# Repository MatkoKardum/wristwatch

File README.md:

# Project Name

## Overview
This project is an electronics/embedded systems project that involves firmware development, PCB design, simulation, and documentation for a device utilizing the DS3232 RTC (Real-Time Clock) and SSD1306 OLED display. The repository provides all necessary resources for development, prototyping, simulation, and deployment.

## Directory Structure
- **Code/**: Contains firmware source code developed using MPLAB IDE.
  - Written in C for a microcontroller (e.g., PIC).
  - Example files: `main.c`, `ds3232.c`, `ssd1306.c`.
- **Datasheets/**: Stores technical documentation for components.
  - Includes: `DS3232.pdf` (Real-Time Clock datasheet), `SSD1306.pdf` (OLED display datasheet).
- **Pcb/**: Contains PCB design files created with KiCAD.
  - Includes schematics and board layouts (e.g., `.sch`, `.kicad_pcb`).
- **Simulation/**: Includes simulation models for Proteus.
  - Contains Proteus project files and schematics (e.g., `.pdsprj`).

## Setup Instructions
1. **Clone the Repository**:
   ```bash
   git clone https://github.com/MatkoKardum/wristwatch
   ```
2. **Code**:
   - Install MPLAB X IDE and the appropriate compiler (e.g., XC8 for PIC microcontrollers).
   - Open the project in `Code/` using MPLAB X IDE.
   - Configure the microcontroller and build the firmware.
3. **PCB Design**:
   - Install KiCAD (version 6 or later recommended).
   - Open PCB files in the `Pcb/` directory using KiCAD.
   - Verify schematics and generate fabrication files as needed.
4. **Simulation**:
   - Install Proteus (version 8 or later recommended).
   - Open simulation files in the `Simulation/` directory using Proteus.
   - Run simulations to validate circuit behavior with DS3232 and SSD1306.
5. **Datasheets**:
   - Reference `DS3232.pdf` and `SSD1306.pdf` in the `Datasheets/` directory for component specifications and pin configurations.

## Requirements
- **Software**:
  - MPLAB X IDE with XC8 compiler (for C firmware development).
  - KiCAD (for PCB design).
  - Proteus (for circuit simulation).
- **Hardware**:
  - Microcontroller compatible with MPLAB (e.g., PIC series).
  - DS3232 Real-Time Clock module.
  - SSD1306 OLED display (I2C or SPI interface).
- **Dependencies**:
  - Ensure MPLAB libraries for DS3232 and SSD1306 are included in `Code/`.
  - Verify Proteus component models for DS3232 and SSD1306 are available.

## Usage
1. **Firmware Development**:
   - Modify source code in `Code/` to implement desired functionality (e.g., timekeeping with DS3232, display output on SSD1306).
   - Compile and flash the firmware using MPLAB X IDE.
2. **PCB Design**:
   - Use KiCAD to modify or finalize PCB layouts in `Pcb/`.
   - Export Gerber files for fabrication.
3. **Simulation**:
   - Run Proteus simulations in `Simulation/` to test circuit behavior before hardware implementation.
4. **Component Reference**:
   - Consult `Datasheets/DS3232.pdf` for RTC configuration (e.g., I2C communication).
   - Refer to `Datasheets/SSD1306.pdf` for OLED display setup (e.g., I2C/SPI settings).

## Contributing
- Fork the repository and create a new branch for your feature or bug fix.
- Submit pull requests with clear descriptions of changes.
- Ensure code follows MPLAB C coding standards and PCB designs are compatible with KiCAD.

## License
This project is licensed under the MIT License - see the `LICENSE` file for details.

## Contact
For questions or support, open an issue on the repository or contact matej.kardum.contact@gmail.com

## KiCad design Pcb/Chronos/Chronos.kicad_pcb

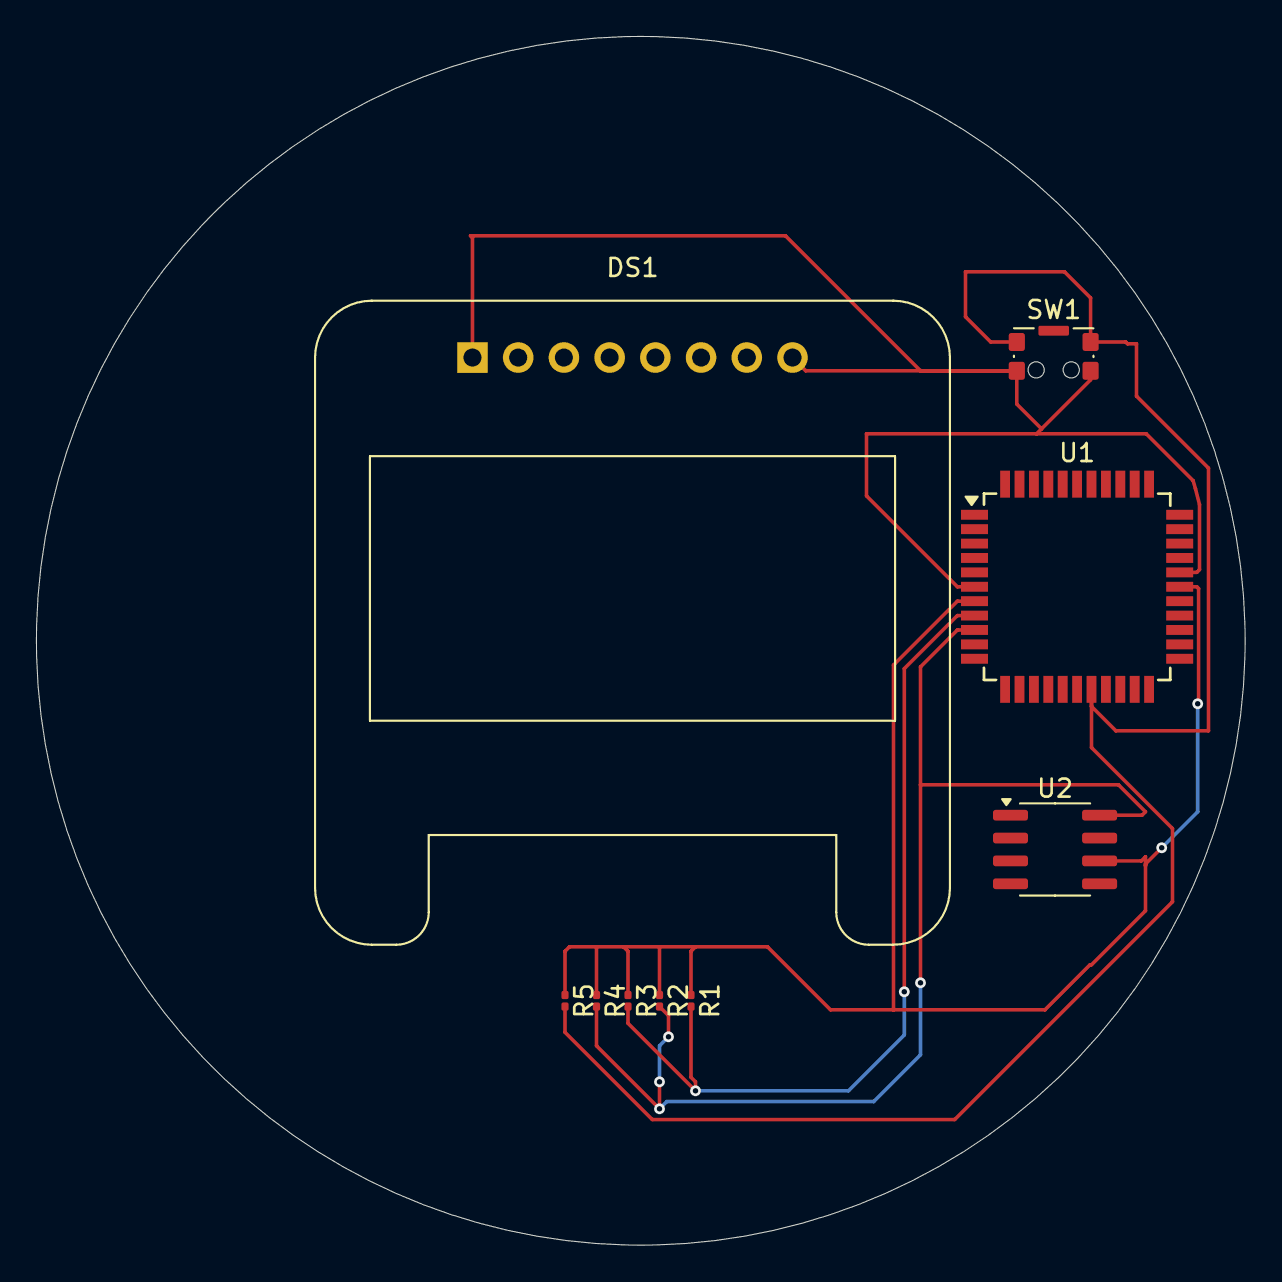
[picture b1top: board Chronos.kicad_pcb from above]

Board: 2 copper layers, 67.1 x 67.1 mm, 9 parts (0 on the bottom side), 5 nets.

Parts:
DS1: OLED-128O064D; Adafruit_SSD1306_No_Mounting_Holes
R1, R2, R3, R4, R5: 4.7k; R_0201_0603Metric
SW1: CK_KMS2xxG; SW_SPST_CK_KMS2xxGP
U1: PIC18F45K50_QFP; TQFP-44_10x10mm_P0.8mm
U2: DS3232M; SOIC-8_3.9x4.9mm_P1.27mm

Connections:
+5V: R1.1, R2.1, R3.1, R4.1, R5.1, U1.7 (VDD), U1.28 (VDD), U2.6 (VBAT)
GND: DS1.1 (GND), DS1.8 (VSS), SW1.2, U1.6 (VSS), U1.29 (VSS)
unnamed: R2.2, R4.2, U1.9 (AN10/C12IN3-/SCK/SCL/INT1/RB1), U2.8 (SCL)
unnamed: R1.2, R3.2, U1.8 (AN12/SRI/~FLT0/SDI/SDA/INT0/RB0), U2.7 (SDA)
unnamed: R5.2, SW1.1, U1.18 (~MCLR/VPP/RE3)

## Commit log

2025-10-06 Added rest of files
2025-10-06 Code
